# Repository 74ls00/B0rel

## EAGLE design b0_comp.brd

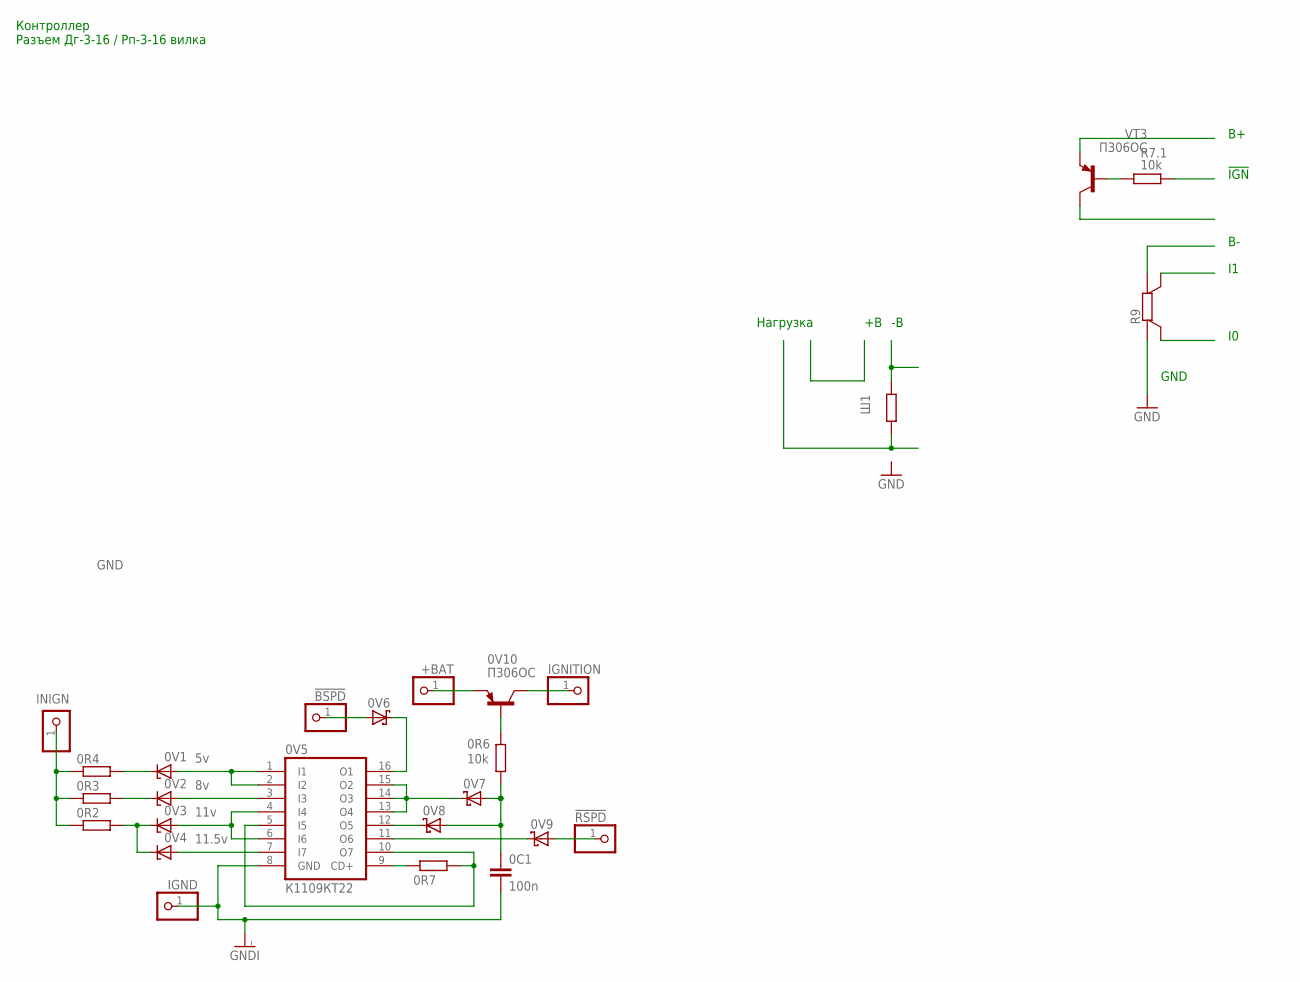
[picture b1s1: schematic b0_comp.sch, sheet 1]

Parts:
0C1: 100n; C0805
0R2, 0R3, 0R4, 0R7: R-EU_R0805; R0805
0R6: 10k; R0805
0V1: 5v; DO34Z7
0V2: 8v; DO34Z7
0V3: 11v; DO34Z7
0V4: 11.5v; DO34Z7
0V5: К1109КТ22; DIL16
0V6, 0V7, 0V8, 0V9: SCHOTTKY-DIODESMD; SMB
0V10: П306ОС; TO92
!BSPD: PINHD-1X1; 1X01
!RSPD: PINHD-1X1; 1X01
+BAT: PINHD-1X1; 1X01
IGND: PINHD-1X1; 1X01
IGNITION: PINHD-1X1; 1X01
INIGN: PINHD-1X1; 1X01
R7.1: 10k; R0805
R9: PMA-A
R_SHUNT: S
VT3: П306ОС; TO92
Ш1: R-EU_R0805; R0805

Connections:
GND: R9.B; also elsewhere on the board
GNDI: 0C1.2, 0V5.8 (GND), IGND.1; also elsewhere on the board
unnamed: 0V5.13 (O4), 0V5.14 (O3), 0V5.15 (O2), 0V7.C
unnamed: 0V3.A, 0V5.4 (I4), 0V5.6 (I6)
unnamed: 0C1.1, 0R6.2, 0V7.A, 0V8.A
unnamed: 0V2.A, 0V5.3 (I3)
unnamed: 0R3.2, 0V2.C
unnamed: 0R2.1, 0R3.1, 0R4.1, INIGN.1
unnamed: 0V1.A, 0V5.1 (I1), 0V5.2 (I2)
unnamed: 0R4.2, 0V1.C
unnamed: 0R6.1, 0V10.2 (B)
unnamed: 0V10.1 (C), IGNITION.1
unnamed: 0V4.A, 0V5.7 (I7)
unnamed: 0R2.2, 0V3.C, 0V4.C
unnamed: 0V6.A, !BSPD.1
unnamed: 0R7.2, 0V5.5 (I5), 0V5.10 (O7)
unnamed: 0V5.11 (O6), 0V9.C
unnamed: 0V9.A, !RSPD.1
unnamed: 0V5.16 (O1), 0V6.C
unnamed: 0V10.3 (E), +BAT.1
unnamed: 0R7.1, 0V5.9 (CD+)
unnamed: 0V5.12 (O5), 0V8.C
unnamed: R7.1.1, VT3.2 (B)

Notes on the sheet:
!IGN
GND
Нагрузка
Контроллер Разъем Дг-3-16 / Рп-3-16 вилка

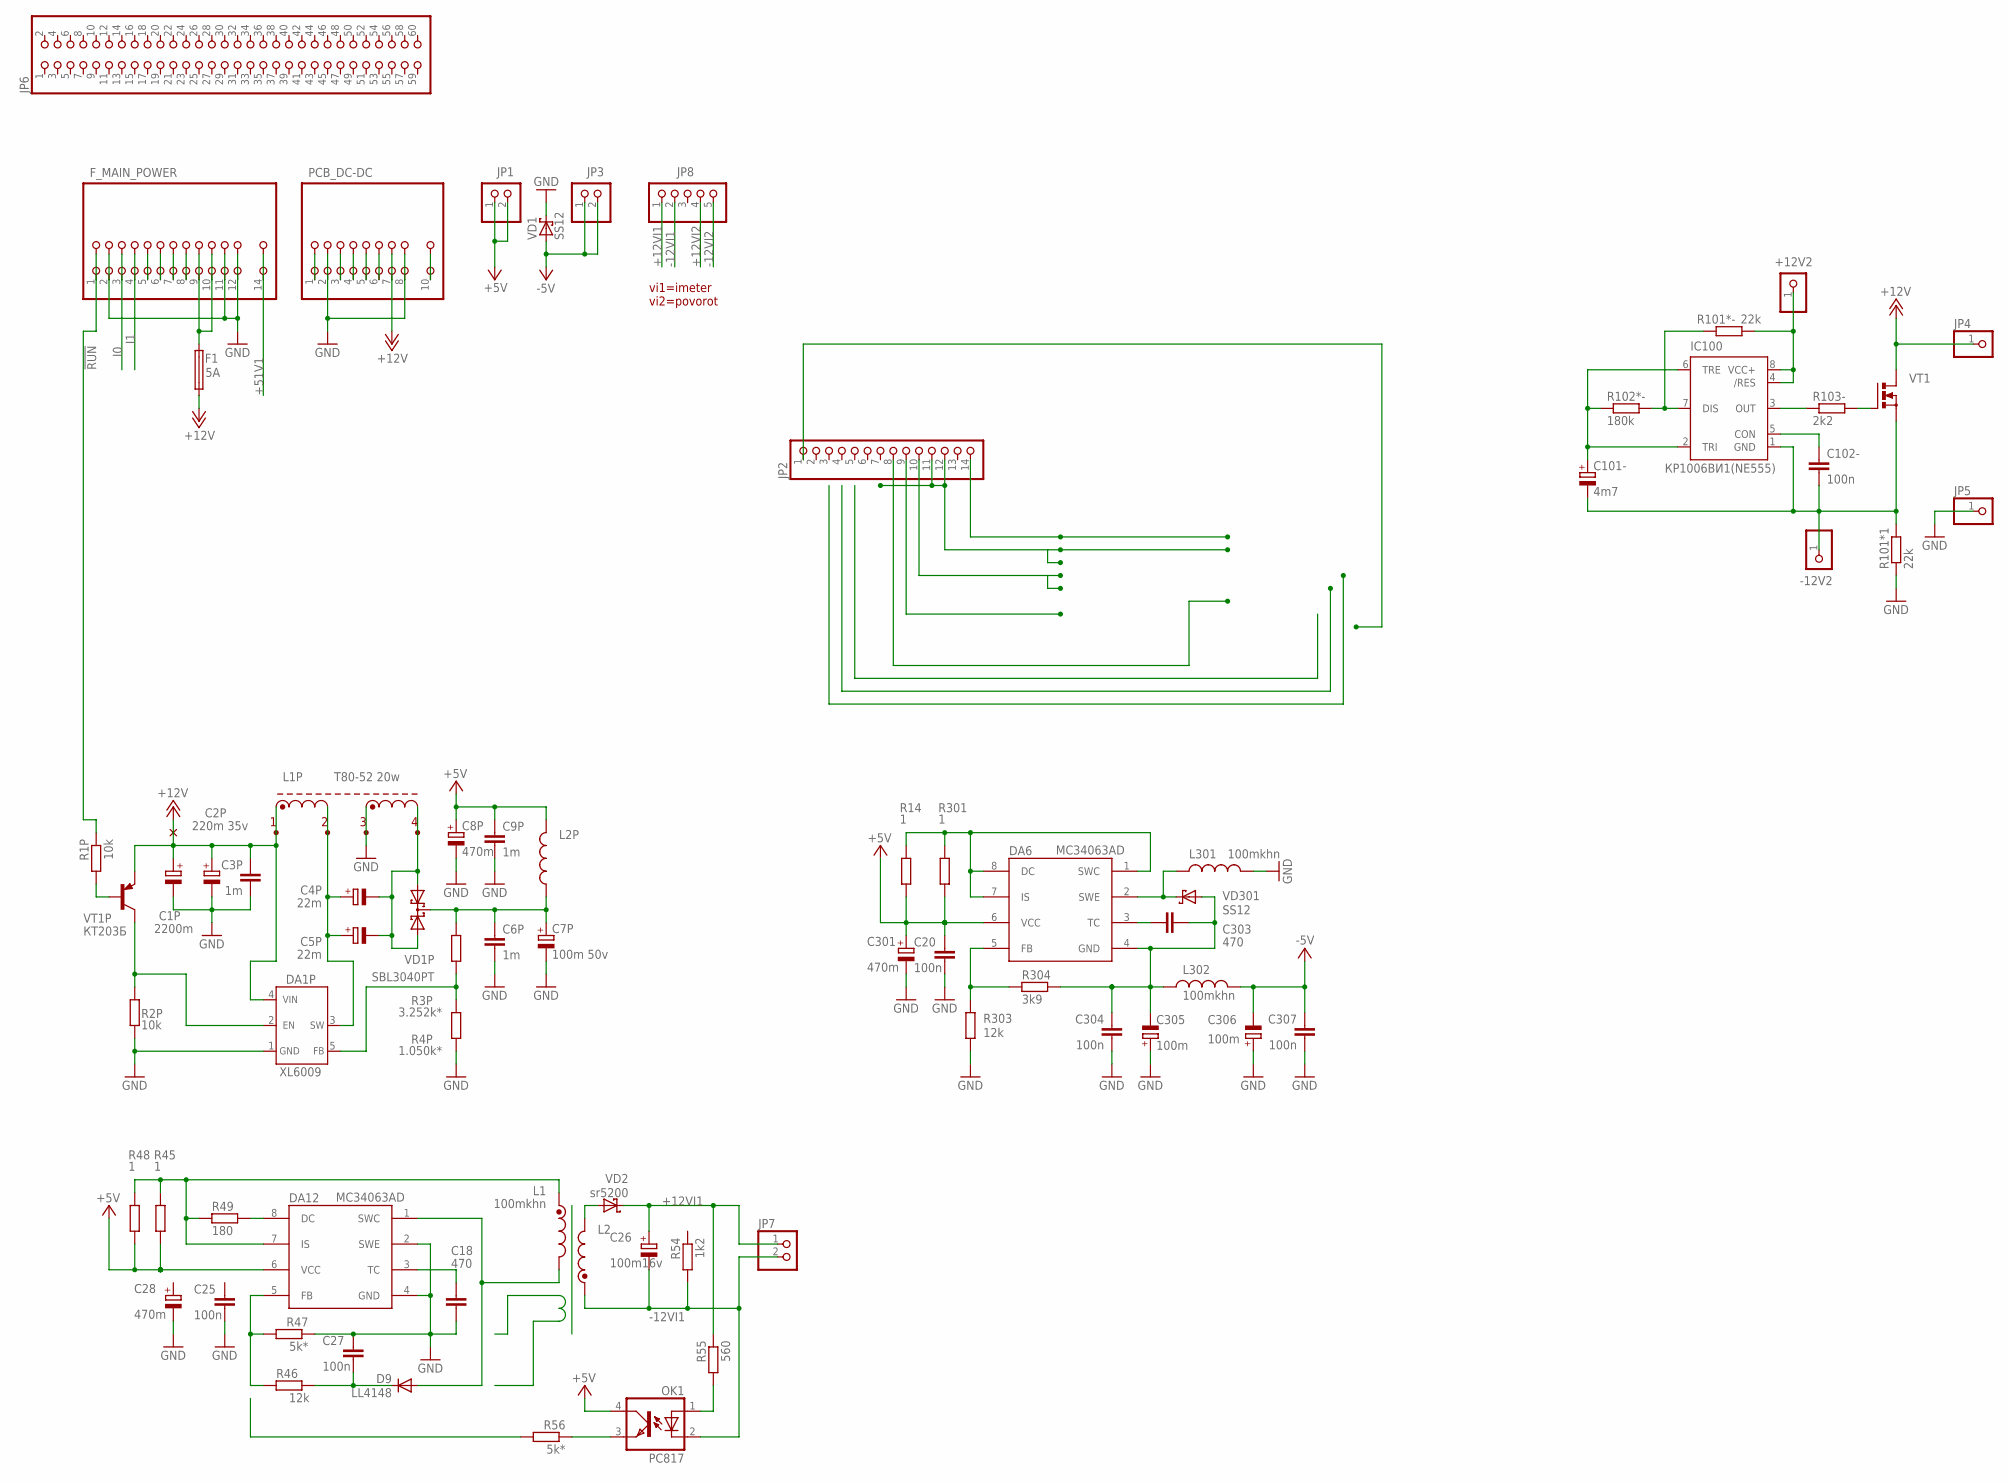
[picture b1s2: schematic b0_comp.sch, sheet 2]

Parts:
1, 2, 3, 4: T_PIN; PIN-2MM
+12V2: PINHD-1X1; 1X01
-12V2: PINHD-1X1; 1X01
C1P: 2200m; E5-13
C2P: 220m 35v; 153CLV-0807
C3P, C6P, C9P: 1m; C0805
C4P, C5P: 22m; E2,5-5
C7P: 100m 50v; 153CLV-0807
C8P: 470m; E5-10,5
C18, C303: 470; C0805
C20, C25, C27, C102-, C304, C307: 100n; C0805
C26: 100m16v; E3,5-8
C28, C301: 470m; E3,5-8
C101-: 4m7; E2-5
C305, C306: 100m; E2,5-5
D9: LL4148; SOD80C
DA1P: XL6009; TO263-5
DA6, DA12: MC34063AD; SOIC8
F1: 5A; SH22,5
F_MAIN_POWER: PINHD-2X14; 2X14
IC100: КР1006ВИ1(NE555); DIL-08
JP1, JP3: PINHD-1X2/2; 1X02
JP2: PINHD-1X14; 1X14
JP4, JP5: PINHD-1X1; 1X01
JP6: PINHD-2X30; 2X30
JP7: PINHD-1X2; 2X01
JP8: PINHD-1X5; 1X05
L1, L301: 100mkhn; TFI0305
L1P: T80-52 20w; R23X14
L2: L-USTFI0410; TFI0410
L2P: L0207/10; 0207/10
L302: 100mkhn; 0204/7
OK1: PC817; DIL04
PCB_DC-DC: PCB_DC-DC
R1P, R2P: 10k; R0805
R3P: 3.252k*; R0805
R4P: 1.050k*; R0805
R14, R45, R48, R301: 1; R1206
R46, R303: 12k; R0805
R47, R56: 5k*; R0805
R49: 180; R0805
R54: 1k2; R0805
R55: 560; R0805
R101*1, R101*-: 22k; R0805
R102*-: 180k; R0805
R103-: 2k2; R0805
R304: 3k9; R0805
VD1, VD301: SS12; SMB
VD1P: SBL3040PT; TO247H
VD2: sr5200; SMB
VT1: MOSFET-N_DPACK; DPACK
VT1P: КТ203Б; TO18

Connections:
!RUN: F_MAIN_POWER.1, F_MAIN_POWER.1A (2), R1P.1
+5V: C8P.+, C9P.1, C20.1, C301.+, DA6.6 (VCC), DA12.6 (VCC), JP1.1, JP1.2, L2P.1, OK1.4 (COL), R14.1, R45.1, R48.1, R301.1; also elsewhere on the board
+12V: 1.1, C1P.+, C2P.+, C3P.1, DA1P.4 (VIN), F1.1, JP4.1, PCB_DC-DC.7 (13), PCB_DC-DC.7@ (14), VT1.D, VT1P.1 (E); also elsewhere on the board
+12VI1: C26.+, JP7.1, JP8.1, R55.1, VD2.C
+12VI2: JP8.4
+51V1: F_MAIN_POWER.14 (27), F_MAIN_POWER.14A (28); also elsewhere on the board
-5V: C306.-, C307.1, JP3.1, JP3.2, L302.2, VD1.A; also elsewhere on the board
-12VI1: C26.-, JP7.2, JP8.2, L2.2, OK1.2 (C), R54.2
-12VI2: JP8.5
GND: 3.1, C1P.-, C2P.-, C3P.2, C6P.2, C7P.-, C8P.-, C9P.2, C18.2, C20.2, C25.2, C27.1, C28.-, C301.-, C304.2, C305.+, C306.+, C307.2, DA1P.1 (GND), DA12.2 (SWE), DA12.4 (GND), F_MAIN_POWER.2 (3), F_MAIN_POWER.2A (4), F_MAIN_POWER.11 (21), F_MAIN_POWER.11A (22), F_MAIN_POWER.12 (23), F_MAIN_POWER.12A (24), JP5.1, L301.2, PCB_DC-DC.2 (3), PCB_DC-DC.2@ (4), PCB_DC-DC.8 (15), PCB_DC-DC.8@ (16), R2P.1, R4P.1, R47.1, R101*1.1, R303.1, VD1.C; also elsewhere on the board
I0: F_MAIN_POWER.3 (5), F_MAIN_POWER.3A (6)
I1: F_MAIN_POWER.4 (7), F_MAIN_POWER.4A (8)
unnamed: IC100.7 (DIS), R101*-.1, R102*-.2
unnamed: C101-.+, IC100.2 (TRI), IC100.6 (TRE), R102*-.1
unnamed: C102-.1, IC100.5 (CON)
unnamed: IC100.3 (OUT), R103-.1
unnamed: R103-.2, VT1.G
unnamed: +12V2.1, IC100.4 (/RES), IC100.8 (VCC+), R101*-.2
unnamed: -12V2.1, C101-.-, C102-.2, IC100.1 (GND), R101*1.2, VT1.S
unnamed: 4.1, C4P.-, C5P.-, VD1P.1 (A1), VD1P.3 (A2)
unnamed: C6P.1, C7P.+, L2P.2, R3P.2, VD1P.2 (C)
unnamed: DA1P.2 (EN), R2P.2, VT1P.3 (C)
unnamed: JP2.11, JP2.12
unnamed: R1P.2, VT1P.2 (B)
unnamed: F_MAIN_POWER.5 (9), F_MAIN_POWER.5A (10)
unnamed: F_MAIN_POWER.6 (11), F_MAIN_POWER.6A (12)
unnamed: F_MAIN_POWER.7 (13), F_MAIN_POWER.7A (14)
unnamed: F_MAIN_POWER.8 (15), F_MAIN_POWER.8A (16)
unnamed: PCB_DC-DC.3 (5), PCB_DC-DC.3@ (6)
unnamed: PCB_DC-DC.5 (9), PCB_DC-DC.5@ (10)
unnamed: F1.2, F_MAIN_POWER.9 (17), F_MAIN_POWER.9A (18), F_MAIN_POWER.10 (19), F_MAIN_POWER.10A (20)
unnamed: PCB_DC-DC.4 (7), PCB_DC-DC.4@ (8)
unnamed: PCB_DC-DC.6 (11), PCB_DC-DC.6@ (12)
unnamed: DA12.5 (FB), R46.1, R47.2
unnamed: PCB_DC-DC.10 (19), PCB_DC-DC.10@ (20)
unnamed: PCB_DC-DC.1, PCB_DC-DC.1@ (2)
unnamed: 2.1, C4P.+, C5P.+, DA1P.3 (SW)
unnamed: DA1P.5 (FB), R3P.1, R4P.2
unnamed: DA6.5 (FB), R303.2, R304.1
unnamed: C303.2, C304.1, C305.-, DA6.4 (GND), L302.1, R304.2, VD301.A
unnamed: D9.A, DA12.1 (SWC), L1.2
unnamed: DA6.1 (SWC), DA6.7 (IS), DA6.8 (DC), R14.2, R301.2
unnamed: DA6.2 (SWE), L301.1, VD301.C
unnamed: C303.1, DA6.3 (TC)
unnamed: DA12.8 (DC), R49.2
unnamed: C18.1, DA12.3 (TC)
unnamed: L2.1, VD2.A
unnamed: DA12.7 (IS), L1.1, R45.2, R48.2, R49.1
unnamed: C27.2, D9.C, R46.2
unnamed: OK1.1 (A), R55.2
unnamed: OK1.3 (EMIT), R56.1

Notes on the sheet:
vi1=imeter vi2=povorot

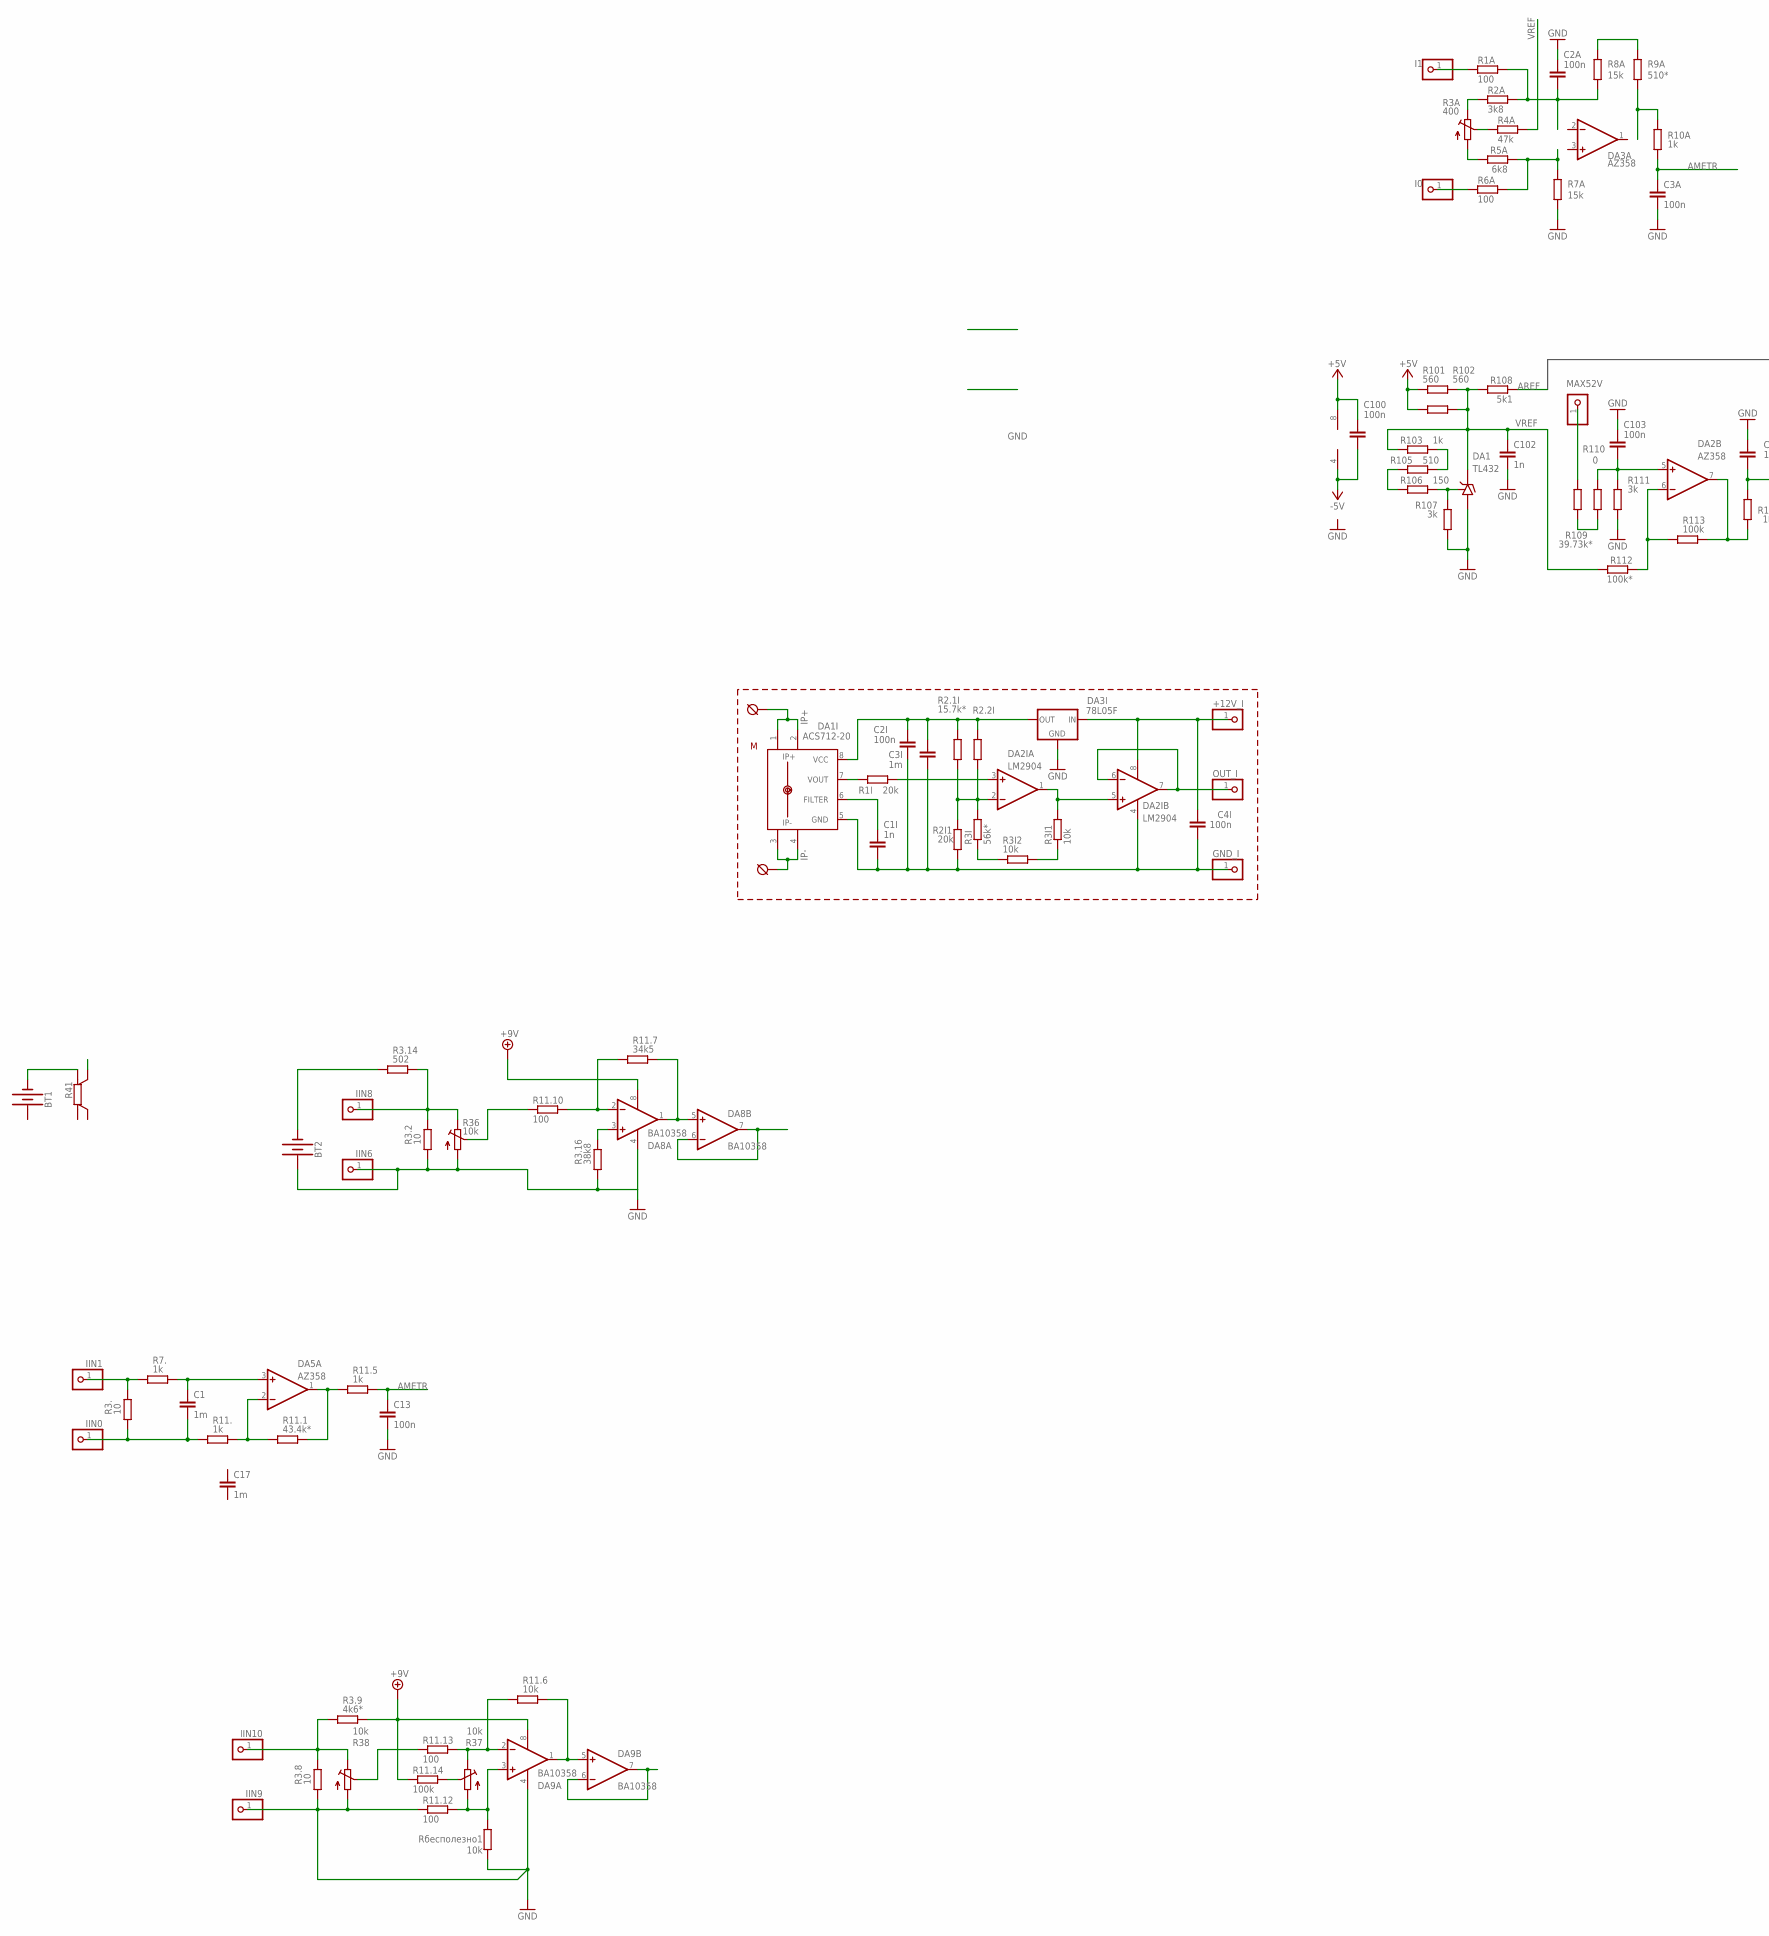
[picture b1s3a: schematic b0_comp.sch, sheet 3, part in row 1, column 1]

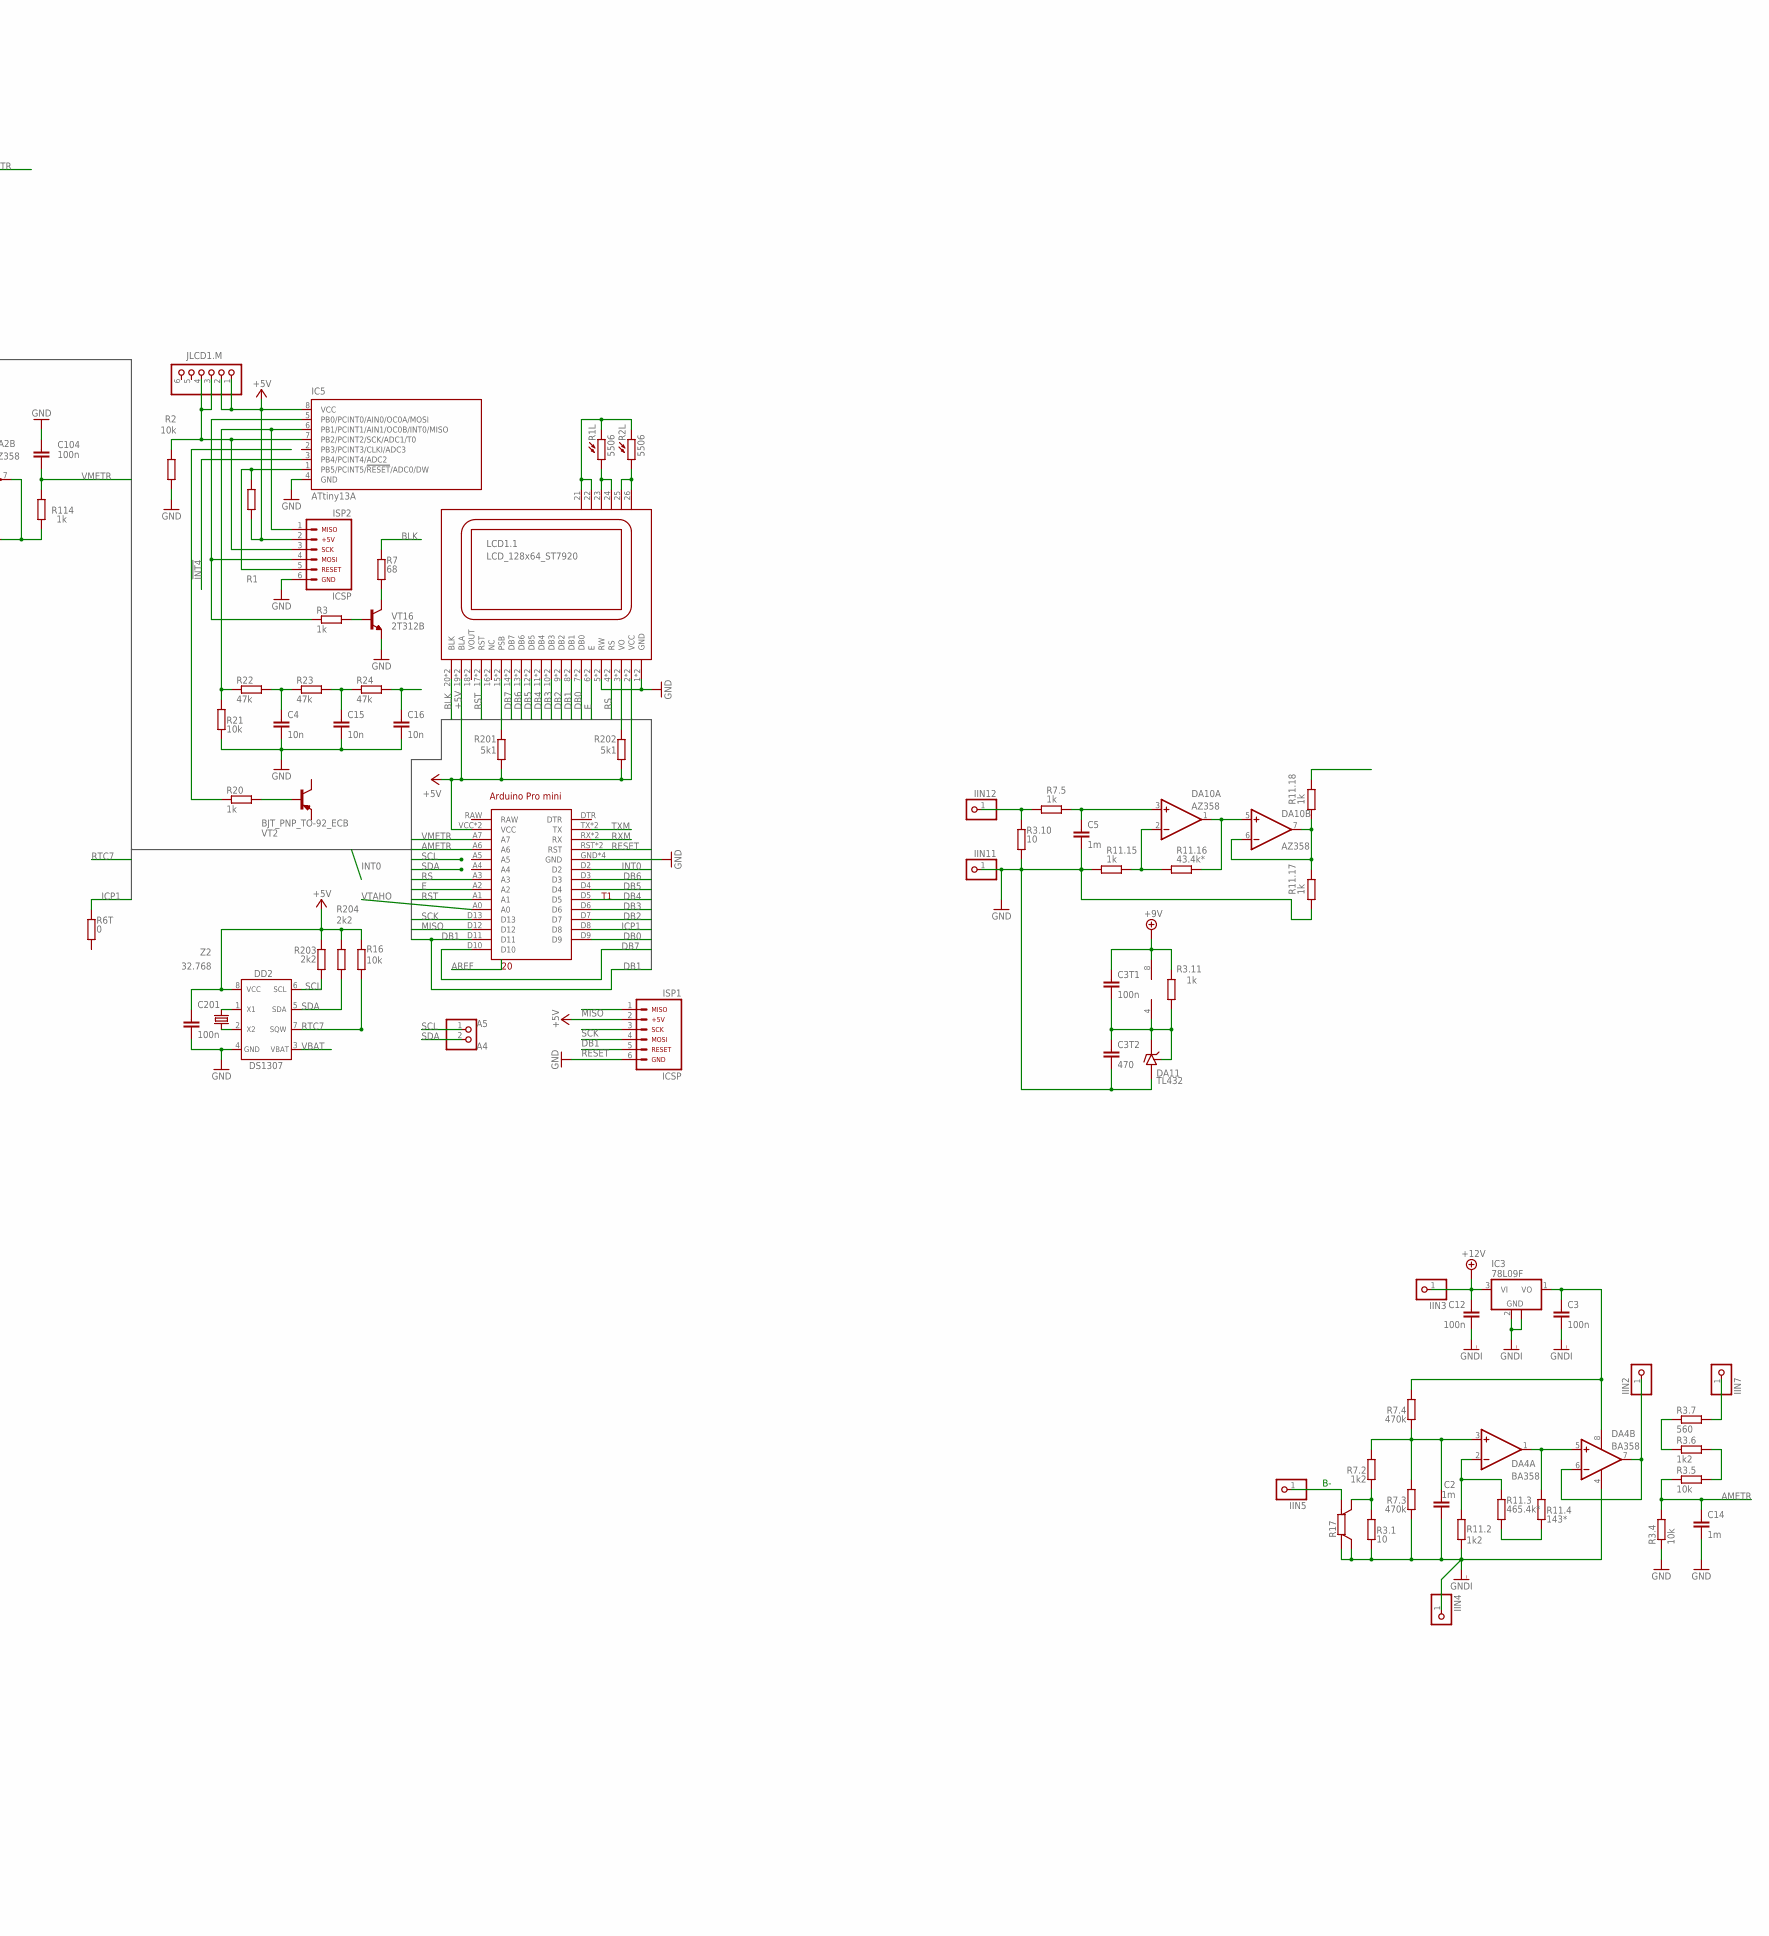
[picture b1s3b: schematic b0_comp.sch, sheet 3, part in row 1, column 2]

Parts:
+12V_I: PINHD-1X1; 1X01
A5: A4; 2X01
ARDUINO1: ARDUINO_PRO_MINI
BT1, BT2: BATTERY-AA
C1, C2, C3I, C5, C14, C17: 1m; C0805
C1I, C102: 1n; C0805
C2A, C2I, C3A, C3T1, C4I, C12, C13, C100, C103, C104, C201: 100n; C0805
C3: 100n; C075-032X103
C3T2: 470; C0805
C4, C15, C16: 10n; C0805
DA1, DA11: TL432; SOT-23
DA1I: ACS712-20; SOIC8
DA2, DA3, DA5, DA10: AZ358; SO08
DA2I: LM2904; SO08
DA3I: 78L05F; SOT89
DA4: BA358; SO08
DA8, DA9: BA10358; SO08
DD2: DS1307; DIL08
GND_I: PINHD-1X1; 1X01
I0, I1: PINHD-1X1; 1X01
IC3: 78L09F; SOT89
IC5: ATtiny13A; DIL08
IIN0, IIN1, IIN2, IIN3, IIN4, IIN5, IIN6, IIN7, IIN8, IIN9, IIN10, IIN11, IIN12: PINHD-1X1; 1X01
ISP1, ISP2: ARDUINO_CONN-ICSP; CONN-2X03
JLCD1.M: PINHD-1X6; 1X06
LCD1: LCD_128x64_ST7920; 12864B
MAX52V: PINHD-1X1; 1X01
OUT_I: PINHD-1X1; 1X01
R1, R2.2I: R-EU_R0805; R0805
R1A, R6A, R11.10, R11.12, R11.13: 100; R0805
R1I, R2I1: 20k; R0805
R1L, R2L: 5506; R_O
R2, R3.4, R3.5, R3I1, R3I2, R11.6, R16, R21: 10k; R0805
R2.1I: 15.7k*; R0805
R2A: 3k8; R0805
R3, R3.11, R7., R7.5, R10A, R11., R11.5, R11.15, R11.17, R11.18, R20, R103, R114: 1k; R0805
R3., R3.1, R3.2, R3.8, R3.10: 10; R0805
R3.6, R7.2, R11.2: 1k2; R0805
R3.7, R101, R102: 560; R0805
R3.9: 4k6*; R0805
R3.14: 502; R0805
R3.16: 38k8; R0805
R3A: 400; RTRIM3296W
R3I: 56k*; R0805
R4A, R22, R23, R24: 47k; R0805
R5A: 6k8; R0805
R6T, R110: 0; R0805
R7: 68; R0805
R7.3, R7.4: 470k; R0805
R7A, R8A: 15k; R0805
R9A: 510*; R0805
R11.1, R11.16: 43.4k*; R0805
R11.3: 465.4k*; R0805
R11.4: 143*; R0805
R11.7: 34k5; R0805
R11.14, R113: 100k; R0805
R17, R41: PMA-A
R36, R37, R38: 10k; RTRIM3202
R105: 510; R0805
R106: 150; R0805
R107, R111: 3k; R0805
R108, R201, R202: 5k1; R0805
R109: 39.73k*; 0207/10
R112: 100k*; R0805
R203, R204: 2k2; R0805
Rбесполезно1: 10k; R0805
U$19: S
U$23, U$24: PIN_D; PIN_D3MM
VT2: BJT_PNP_TO-92_ECB; TO92
VT16: 2Т312В; TO92
Z2: 32.768; FC-12M

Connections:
1: LCD1.21 (1), LCD1.22 (2), R1L.P$1 (1), R2L.P$1 (1)
!INT4: IC5.3 (PB4/PCINT4/ADC2)
+: BT1.PWR@1 (+)
+5V: ARDUINO1.VCC, ARDUINO1.VCC@1 (VCC), C100.1, C201.1, DA2.8 (V+), DD2.8 (VCC), IC5.8 (VCC), ISP1.2, ISP2.2, JLCD1.M.1, JLCD1.M.2, LCD1.2 (VCC), LCD1.2@ (VCC), LCD1.19 (BLA), LCD1.19@ (BLA), R1.1, R16.2, R101.1, R102.2, R201.1, R202.1, R203.2, R204.2; also elsewhere on the board
+5VI: C2I.1, C3I.1, DA1I.8 (VCC), DA3I.1 (OUT), R2.1I.2, R2.2I.2
+9V: C3T1.1, DA8.8 (V+), DA9.8 (V+), DA10.8 (V+), R3.9.2, R3.11.2, R11.14.1
+12V: C12.1, IC3.3 (VI), IIN3.1; also elsewhere on the board
+12VI: +12V_I.1, C4I.1, DA2I.8 (V+), DA3I.3 (IN)
+51V1: MAX52V.1, R109.1; also elsewhere on the board
-5V: C100.2, DA2.4 (V-); also elsewhere on the board
AMETR: ARDUINO1.A6, C3A.1, C13.1, C14.1, R3.4.2, R3.5.1, R10A.1, R11.5.2
AREF: R108.1
AREF2V5: DA1.1 (R), R106.1, R107.2
BLK: LCD1.20 (BLK), LCD1.20@ (BLK), R7.2
DB0: ARDUINO1.D9, LCD1.7 (DB0), LCD1.7@ (DB0)
DB1: ARDUINO1.D11, ISP1.4, LCD1.8 (DB1), LCD1.8@ (DB1); also elsewhere on the board
DB2: ARDUINO1.D7, LCD1.9 (DB2), LCD1.9@ (DB2)
DB3: ARDUINO1.D6, LCD1.10 (DB3), LCD1.10@ (DB3)
DB4: ARDUINO1.D5, LCD1.11 (DB4), LCD1.11@ (DB4)
DB5: ARDUINO1.D4, LCD1.12 (DB5), LCD1.12@ (DB5)
DB6: ARDUINO1.D3, LCD1.13 (DB6), LCD1.13@ (DB6)
DB7: ARDUINO1.D10, LCD1.14 (DB7), LCD1.14@ (DB7)
E: ARDUINO1.A2, LCD1.6 (E), LCD1.6@ (E)
GND: ARDUINO1.GND, ARDUINO1.GND@1 (GND), ARDUINO1.GND@2 (GND), ARDUINO1.GND@3 (GND), BT2.PWR@1 (+), C2A.1, C3A.2, C3T2.2, C4.2, C5.2, C13.2, C14.2, C15.2, C16.2, C102.2, C103.1, C104.1, C201.2, DA1.3 (A), DA3I.2 (GND), DA3I.2@1 (GND), DA8.4 (V-), DA9.4 (V-), DA11.3 (A), DD2.4 (GND), IC5.4 (GND), IIN6.1, IIN9.1, IIN11.1, ISP1.6, ISP2.6, LCD1.1 (GND), LCD1.1@ (GND), LCD1.5 (RW), LCD1.5@ (RW), R2.1, R3.2.1, R3.4.1, R3.8.1, R3.10.1, R3.16.1, R7A.1, R11.12.1, R11.15.1, R11.17.1, R21.1, R36.1 (A), R38.1 (A), R107.1, R111.1, Rбесполезно1.1, VT16.3 (E); also elsewhere on the board
GNDI: C1I.2, C2.2, C2I.2, C3.2, C3I.2, C4I.2, C12.2, DA1I.5 (GND), DA2I.4 (V-), DA4.4 (V-), GND_I.1, IC3.2 (GND), IC3.2@1 (GND), IIN4.1, R2I1.1, R3.1.1, R7.3.1, R11.2.1, R17.B, R17.SB; also elsewhere on the board
ICP1: ARDUINO1.D8, R6T.2
INT0: ARDUINO1.D2
IP+: DA1I.1 (IP+), DA1I.2 (IP+1), U$23.P$1
IP-: DA1I.3 (IP-), DA1I.4 (IP-1), U$24.P$1
MISO: ARDUINO1.D12, ISP1.1; also elsewhere on the board
MISO13: IC5.6 (PB1/PCINT1/AIN1/OC0B/INT0/MISO), ISP2.1, R21.2, R22.1
MOSI13: IC5.5 (PB0/PCINT0/AIN0/OC0A/MOSI), ISP2.4, R3.1
unnamed: LCD1.3 (VO), LCD1.3@ (VO), R202.2
unnamed: LCD1.15 (PSB), LCD1.15@ (PSB), R201.2
unnamed: C103.2, DA2.5 (+IN), R110.1, R111.2
unnamed: DA5.2 (-IN), R11..2, R11.1.1
unnamed: R3.2, VT16.2 (B)
unnamed: R109.2, R110.2
unnamed: R20.2, VT2.3 (B)
unnamed: C4.1, R22.2, R23.1
unnamed: C1.1, DA5.3 (+IN), R7..2
unnamed: DA2.7 (OUT), R113.2, R114.1
unnamed: IIN1.1, R3..2, R7..1
unnamed: DA2.6 (-IN), R112.1, R113.1
unnamed: R103.1, R105.1
unnamed: R105.2, R106.2
unnamed: DA8.3 (+IN), R3.16.2
unnamed: R8A.2, R9A.1
unnamed: IIN8.1, R3.2.2, R3.14.2, R36.3 (E)
unnamed: R11.10.1, R36.2 (S)
unnamed: DA8.1 (OUT), DA8.5 (+IN), R11.7.2
unnamed: C15.1, R23.2, R24.1
unnamed: DD2.1 (X1), Z2.P$2 (2)
unnamed: C16.1, R24.2
unnamed: DD2.2 (X2), Z2.P$1 (1)
unnamed: DA8.2 (-IN), R11.7.1, R11.10.2
unnamed: DA8.6 (-IN), DA8.7 (OUT)
unnamed: R7.1, VT16.1 (C)
unnamed: LCD1.25 (5), LCD1.26 (6), R2L.P$2 (2)
unnamed: LCD1.23 (3), LCD1.24 (4), R1L.P$2 (2)
unnamed: DA9.3 (+IN), R11.12.2, R37.1 (A), Rбесполезно1.2
unnamed: IIN10.1, R3.8.2, R3.9.1, R38.3 (E)
unnamed: DA9.1 (OUT), DA9.5 (+IN), R11.6.2
unnamed: DA9.2 (-IN), R11.6.1, R11.13.2, R37.3 (E)
unnamed: R11.14.2, R37.2 (S)
unnamed: DA9.6 (-IN), DA9.7 (OUT)
unnamed: R11.13.1, R38.2 (S)
unnamed: DA10.2 (-IN), R11.15.2, R11.16.1
unnamed: R3I.1, R3I2.1
unnamed: DA4.2 (-IN), R11.2.2, R11.3.1
unnamed: C2.1, DA4.3 (+IN), R7.2.2, R7.3.2, R7.4.1
unnamed: R3.1.2, R7.2.1, R17.SA
unnamed: DA4.1 (OUT), DA4.5 (+IN), R11.4.2
unnamed: DA4.6 (-IN), DA4.7 (OUT), IIN2.1
unnamed: IIN5.1, R17.A
unnamed: R11.3.2, R11.4.1
unnamed: C3.1, DA4.8 (V+), IC3.1 (VO), R7.4.2
unnamed: R3.5.2, R3.6.2
unnamed: R3.6.1, R3.7.1
unnamed: C1.2, IIN0.1, R3..1, R11..1
unnamed: DA5.1 (OUT), R11.1.2, R11.5.1
unnamed: R3A.1 (A), R5A.2
unnamed: IIN7.1, R3.7.2
unnamed: C5.1, DA10.3 (+IN), R7.5.2
unnamed: IIN12.1, R3.10.2, R7.5.1
unnamed: DA10.1 (OUT), DA10.5 (+IN), R11.16.2
unnamed: C3T1.2, C3T2.1, DA10.4 (V-), DA11.1 (R), DA11.2 (C), R3.11.1
unnamed: R5A.1, R6A.2, R7A.2
unnamed: I0.1, R6A.1
unnamed: R9A.2, R10A.2
unnamed: C2A.2, R1A.2, R2A.2, R8A.1
unnamed: R3A.2 (S), R4A.1
unnamed: I1.1, R1A.1
unnamed: DA10.6 (-IN), DA10.7 (OUT), R11.17.2, R11.18.1
unnamed: R2A.1, R3A.3 (E)
unnamed: DA2I.6 (-IN), DA2I.7 (OUT), OUT_I.1
unnamed: R3I1.1, R3I2.2
unnamed: BT1.GND@1 (-), R41.B
unnamed: BT2.GND@1 (-), R3.14.1
unnamed: C1I.1, DA1I.6 (FILTER)
unnamed: DA1I.7 (VOUT), R1I.2
unnamed: DA2I.3 (+IN), R1I.1
unnamed: DA2I.1 (OUT), DA2I.5 (+IN), R3I1.2
unnamed: DA2I.2 (-IN), R2.1I.1, R2.2I.1, R2I1.2, R3I.2
RES13: IC5.1 (PB5/PCINT5/!RESET!/ADC0/DW), ISP2.5, R1.2
RESET: ARDUINO1.RST, ARDUINO1.RST@1 (RST), ISP1.5; also elsewhere on the board
RS: ARDUINO1.A3, LCD1.4 (RS), LCD1.4@ (RS)
RST: ARDUINO1.A1, LCD1.17 (RST), LCD1.17@ (RST)
RTC7: DD2.7 (SQW), R16.1; also elsewhere on the board
RXM: ARDUINO1.RX, ARDUINO1.RX@1 (RX)
SCK: ARDUINO1.D13, ISP1.3; also elsewhere on the board
SCK13: IC5.7 (PB2/PCINT2/SCK/ADC1/T0), ISP2.3, JLCD1.M.3, JLCD1.M.4, R2.2
SCL: A5.1, DD2.6 (SCL), R203.1; also elsewhere on the board
SDA: A5.2, DD2.5 (SDA), R204.1; also elsewhere on the board
TXM: ARDUINO1.TX, ARDUINO1.TX@1 (TX)
V+: DA3.8 (V+), DA5.8 (V+)
V-: DA3.4 (V-), DA5.4 (V-)
VBAT: DD2.3 (VBAT); also elsewhere on the board
VMETR: ARDUINO1.A7, C104.2, R114.2; also elsewhere on the board
VREF: C102.1, DA1.2 (C), R4A.2, R101.2, R102.1, R103.2, R108.2, R112.2
VTAHO: ARDUINO1.A0

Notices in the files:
parts and their libraries:
SparkFun-Batteries: Licensing: Creative Commons ShareAlike 4.0 International - https://creativecommons.org/licenses/by-sa/4.0
